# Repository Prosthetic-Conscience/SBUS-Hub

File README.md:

# SBUS-Hub

This is a schematic for a short SBUS or SBUS.2 Hub. It uses square pin header pins on male side, and commonly available female headers from digikey for the female/RX side

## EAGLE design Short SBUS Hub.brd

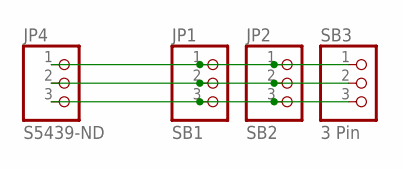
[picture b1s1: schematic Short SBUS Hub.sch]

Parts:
JP1: SB1; 1X03
JP2: SB2; 1X03
JP4: S5439-ND; 1X03
SB3: 3 Pin; 1X03

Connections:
unnamed: JP1.3, JP2.3, JP4.3, SB3.3
unnamed: JP1.2, JP2.2, JP4.2, SB3.2
unnamed: JP1.1, JP2.1, JP4.1, SB3.1

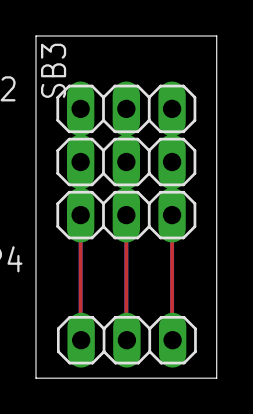
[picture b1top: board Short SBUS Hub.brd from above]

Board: 2 copper layers, 10.0 x 19.0 mm, 4 parts (0 on the bottom side), 3 nets.
